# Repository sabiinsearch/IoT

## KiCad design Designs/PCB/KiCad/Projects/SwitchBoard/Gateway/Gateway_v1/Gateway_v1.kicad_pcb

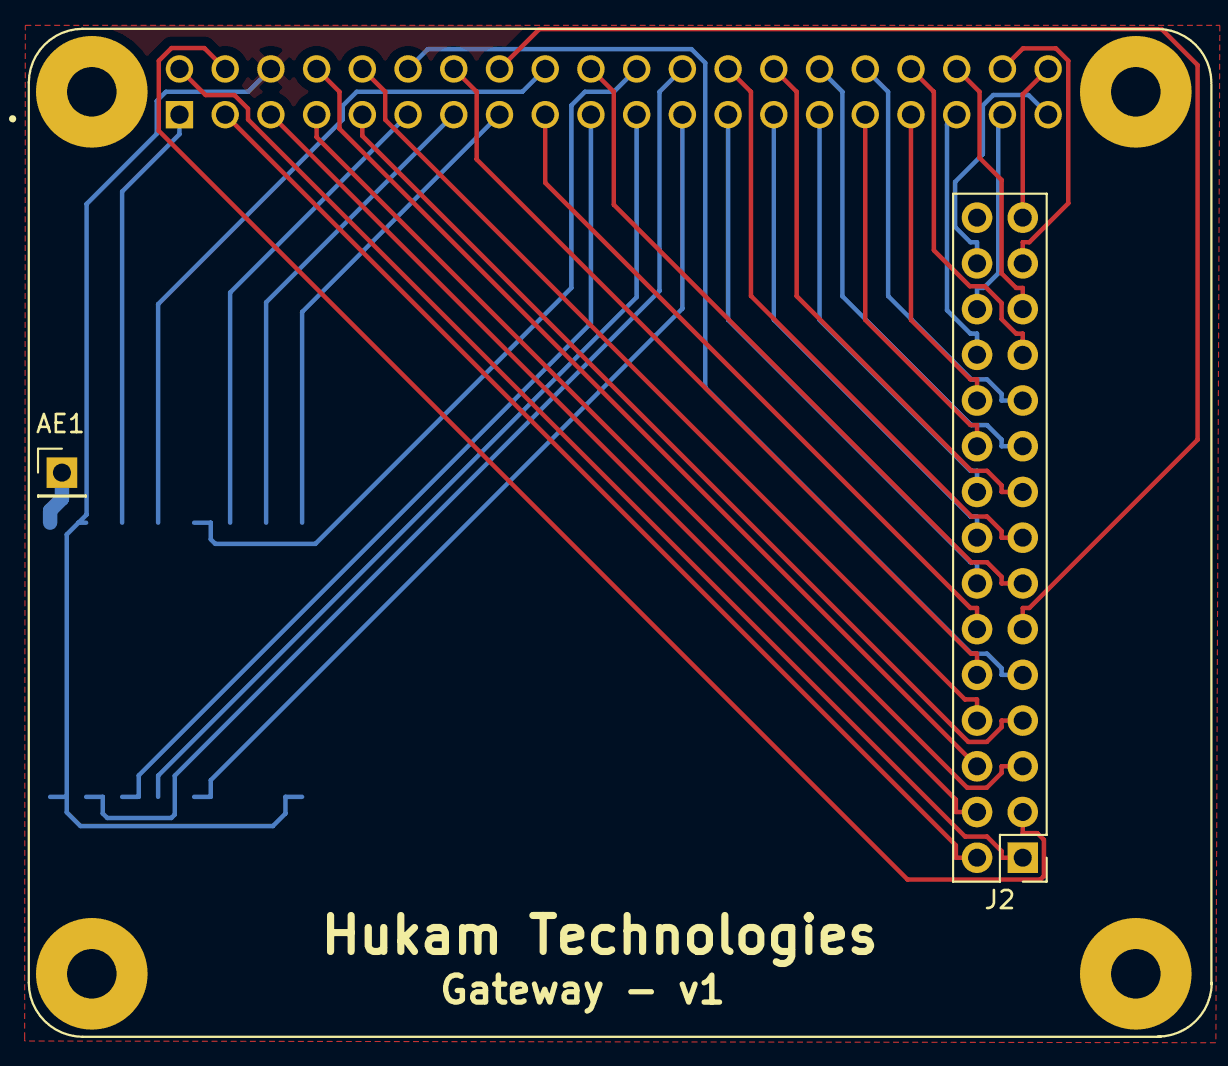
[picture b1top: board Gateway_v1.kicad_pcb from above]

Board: 2 copper layers, 4 parts (1 on the bottom side), 41 nets.

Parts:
AE1: Antenna; PinHeader_1x01_P2.54mm_Vertical
J1: Raspberry_Pi_2_3; MODULE_RASPBERRY_PI_3_MODEL_B+
J2: Conn_usable_pins; PinHeader_2x15_P2.54mm_Vertical
U1: LoRa

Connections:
/3.3v: J1.1, U1.3
/DIO0: J1.22, U1.5
/DIO1: J1.11, U1.6
/DIO2: J1.13, U1.7
/DIO3: J1.15, U1.8
/Gnd: J1.6, U1.2, U1.9, U1.16
/MISO: J1.21, U1.13
/MOSI: J1.19, U1.14
/NSS: J1.24, U1.15
/Pin_2: J1.2, J2.1
/Pin_3: J1.3, J2.2
/Pin_4: J1.4, J2.3
/Pin_5: J1.5, J2.4
/Pin_7: J1.7, J2.5
/Pin_8: J1.8, J2.6
/Pin_9: J1.9, J2.7
/Pin_10: J1.10, J2.8
/Pin_12: J1.12, J2.9
/Pin_14: J1.14, J2.10
/Pin_16: J1.16, J2.11
/Pin_17: J1.17, J2.12
/Pin_20: J1.20, J2.13
/Pin_25: J1.25, J2.14
/Pin_26: J1.26, J2.15
/Pin_27: J1.27, J2.16
/Pin_28: J1.28, J2.17
/Pin_29: J1.29, J2.18
/Pin_30: J1.30, J2.19
/Pin_31: J1.31, J2.20
/Pin_32: J1.32, J2.21
/Pin_33: J1.33, J2.22
/Pin_34: J1.34, J2.23
/Pin_35: J1.35, J2.24
/Pin_36: J1.36, J2.25
/Pin_37: J1.37, J2.26
/Pin_38: J1.38, J2.27
/Pin_39: J1.39, J2.28
/Pin_40: J1.40, J2.29
/Reset: J1.18, U1.4
/SCK: J1.23, U1.12
unnamed: AE1.1, U1.1

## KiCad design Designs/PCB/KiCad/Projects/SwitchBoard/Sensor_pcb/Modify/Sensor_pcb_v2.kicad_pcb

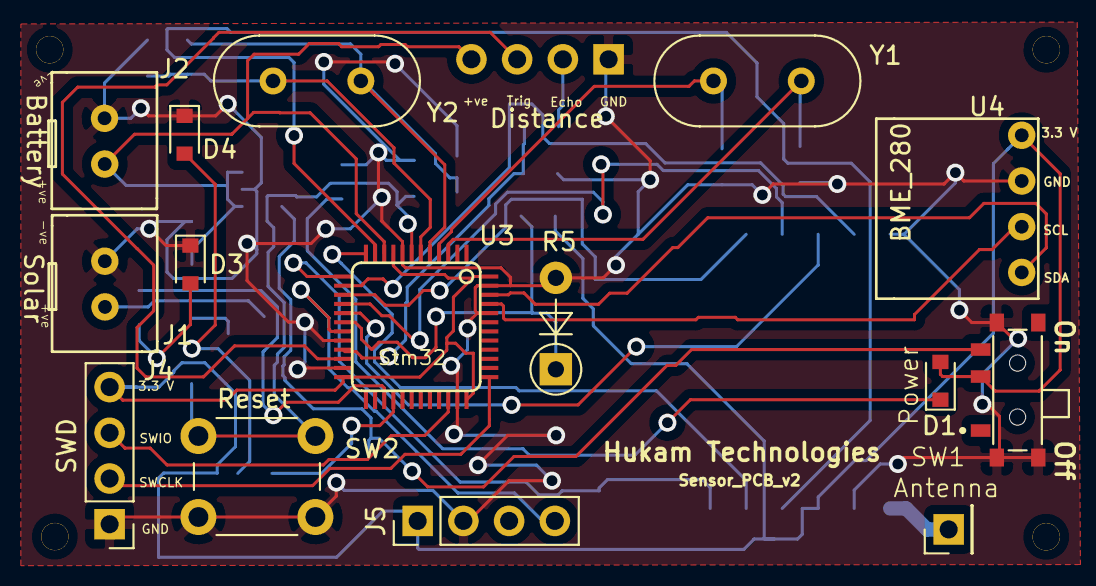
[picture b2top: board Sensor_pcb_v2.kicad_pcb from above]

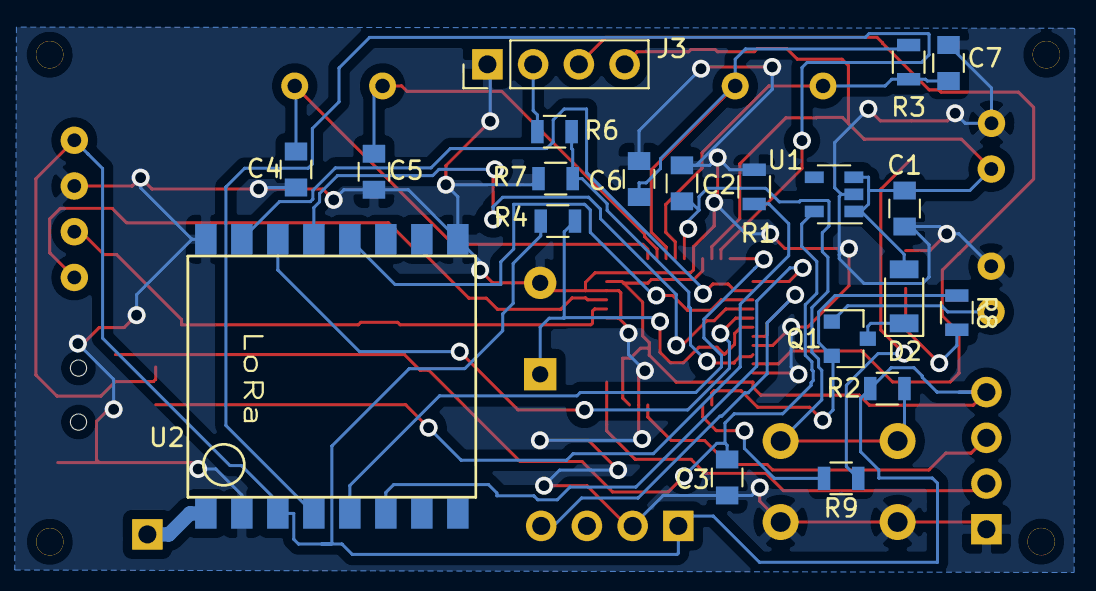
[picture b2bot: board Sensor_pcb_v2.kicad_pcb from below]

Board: 2 copper layers, 39 parts (20 on the bottom side), 33 nets.

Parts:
AE1: Antenna; Pin_Header_Straight_1x01_Pitch2.54mm
C1, C3: 100 nf; C_0805
C2: 1.0uf; C_0805
C4, C5, C6, C7: 20pf; C_0805
D1, D3: Pwr_L.E.D; D_0805
D2: DIODE; D_1206
D4: Bat_Low; D_0805
J1: Solar_input; Battery_holder
J2: Battery_input; Battery_holder
J3: Distance /; Pin_Header_Straight_1x04_Pitch2.54mm
J4: SWD; Pin_Header_Straight_1x04_Pitch2.54mm
J5: Airquality; Pin_Header_Straight_1x04_Pitch2.54mm
M1, M2, M3, M4: MountingHole_1.5mm; MountingHole1.5mm
Q1: BC547; SOT-23
R1, R8, R9: 510 R; R_0805
R2, R4: 10K; R_0805
R3: 1M; R_0805
R5: LDR; D_A-405_P5.08mm_Vertical_AnodeUp
R6: 2.7K; R_0805
R7: 4.7K; R_0805
SW1: MLL1200S; SW_MLL1200S
SW2: SW_Push; SW_PUSH_6mm_h5mm
U1: APK2112.K-3.3; SOT-23-5
U2: LoRa
U3: STM32; STM32(LQFP48)
U4: BME_280; BME280
Y1: 32.768K; Crystal_HC49-4H_Vertical
Y2: 8Mhz; Crystal_HC49-4H_Vertical

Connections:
/Air_in: J5.4, U3.19
/BAT_IN: C1.2, D2.2, J2.2, J3.4, U1.1, U1.3, U3.10
/Charge: Q1.2, R8.1, U3.27
/DIO0: U2.5, U3.12
/DIO1: U2.6, U3.13
/Echo: J3.2, R6.2
/EchoToStm32: R6.1, R7.2, U3.21
/GND: C1.1, C2.1, C3.1, C4.2, C5.2, C6.2, C7.2, D3.1, D4.1, J1.1, J2.1, J3.1, J4.1, J5.2, R1.2, R5.2, R7.1, SW1.G1, SW1.G2, SW1.G3, SW2.1, U1.2, U2.2, U2.9, U2.16, U3.8, U3.20, U3.23, U3.35, U3.44, U3.47, U4.2
/LDR_IN: R4.1, R5.1, U3.18
/MISO: U2.13, U3.16
/MOSI: U2.14, U3.17
/NSS: U2.15, U3.14
/OSCIN: C6.1, R3.1, U3.5, Y2.1
/OSCOUT: C7.1, R3.2, U3.6, Y2.2
/PC14: C4.1, U3.3, Y1.1
/PC15: C5.1, U3.4, Y1.2
/RESET: C2.2, R2.2, SW2.2, U3.7
/Reset_LoRa: U2.4, U3.11
/SCK: U2.12, U3.15
/SCL: U3.45, U4.3
/SDA: U3.46, U4.4
/SWCLK: J4.2, U3.37
/SWIO: J4.3, U3.34
/Solar_+ve: J1.2, Q1.1
/Supply_Reg: C3.2, SW1.3, U1.5
/Trig: J3.3, U3.22
/VCC3V3: D1.2, J4.4, J5.1, R2.1, R4.2, SW1.2, U2.3, U3.9, U3.24, U3.36, U3.48, U4.1
unnamed: AE1.1, U2.1
unnamed: D1.1, R1.1
unnamed: D2.1, Q1.3
unnamed: D3.2, R8.2
unnamed: D4.2, R9.1
unnamed: R9.2, U3.28

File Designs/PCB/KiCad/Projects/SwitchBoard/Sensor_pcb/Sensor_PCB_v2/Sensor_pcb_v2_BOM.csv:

Reference,,Quantity,,Footprint / package,,,,Datasheet,,Spice_Netlist_Enabled,,Spice_Primitive
AE1,,1,Antenna,Pin_Headers:Pin_Header_Straight_1x01_Pitch2.54mm,,,,,,,,
C2,,1,1.0uf,Capacitors_SMD:C_0805,,,,,,,,
"C1, C3",,2,100nf,Capacitors_SMD:C_0805,,,,,,,,
"C4, C5, C6, C7",,4,20pf,Capacitors_SMD:C_0805,,,,~,,,,
"D1, D3",,2,Pwr_L.E.D,Diodes_SMD:D_0805,,,,,,,,
D2,,1,DIODE,Diodes_SMD:D_1206,,,,,,,,
D4,,1,Bat_Low,Diodes_SMD:D_0805,,,,,,,,
J1,,1,Solar_input,Custom_Libraries:Battery_holder,,,,,,,,
J2,,1,Battery_input,Custom_Libraries:Battery_holder,,,,,,,,
J3,,1,Distance /,Pin_Headers:Pin_Header_Straight_1x04_Pitch2.54mm,,,,,,,,
J4,,1,SWD,Pin_Headers:Pin_Header_Straight_1x04_Pitch2.54mm,,,,,,,,
J5,,1,Airquality,Pin_Headers:Pin_Header_Straight_1x04_Pitch2.54mm,,,,,,,,
Q1,,1,BC547,TO_SOT_Packages_SMD:SOT-23,,,,,,,,
"R1, R8, R9",,3,510 R,Resistors_SMD:R_0805,,,,,,,,
"R2, R4",,2,10K,Resistors_SMD:R_0805,,,,,,,,
R3,,1,1M,Resistors_SMD:R_0805,,,,,,,,
R5,,1,LDR,Diodes_THT:D_A-405_P5.08mm_Vertical_AnodeUp,,,,,,,,
R6,,1,2.7K,Resistors_SMD:R_0805,,,,,,,,
R7,,1,4.7K,Resistors_SMD:R_0805,,,,,,,,
SW1,,1,MLL1200S,Custom_Libraries:SW_MLL1200S,,,,,,,,
SW2,,1,SW_Push,Buttons_Switches_THT:SW_PUSH_6mm_h5mm,,,,,,,,
U1,,1,APK2112.K-3.3,TO_SOT_Packages_SMD:SOT-23-5,,,,,,,,
U2,,1,LoRa,Custom_Libraries:LoRa,,,,,,,,
U3,,1,STM32,Custom_Libraries:STM32(LQFP48),,,,,,,,
U4,,1,BME_280,Custom_Libraries:BME280,,,,,,,,
Y1,,1,32.768K,Crystals:Crystal_HC49-4H_Vertical,,,,,,,,
Y2,,1,8Mhz,Crystals:Crystal_HC49-4H_Vertical,~,,,,,,,

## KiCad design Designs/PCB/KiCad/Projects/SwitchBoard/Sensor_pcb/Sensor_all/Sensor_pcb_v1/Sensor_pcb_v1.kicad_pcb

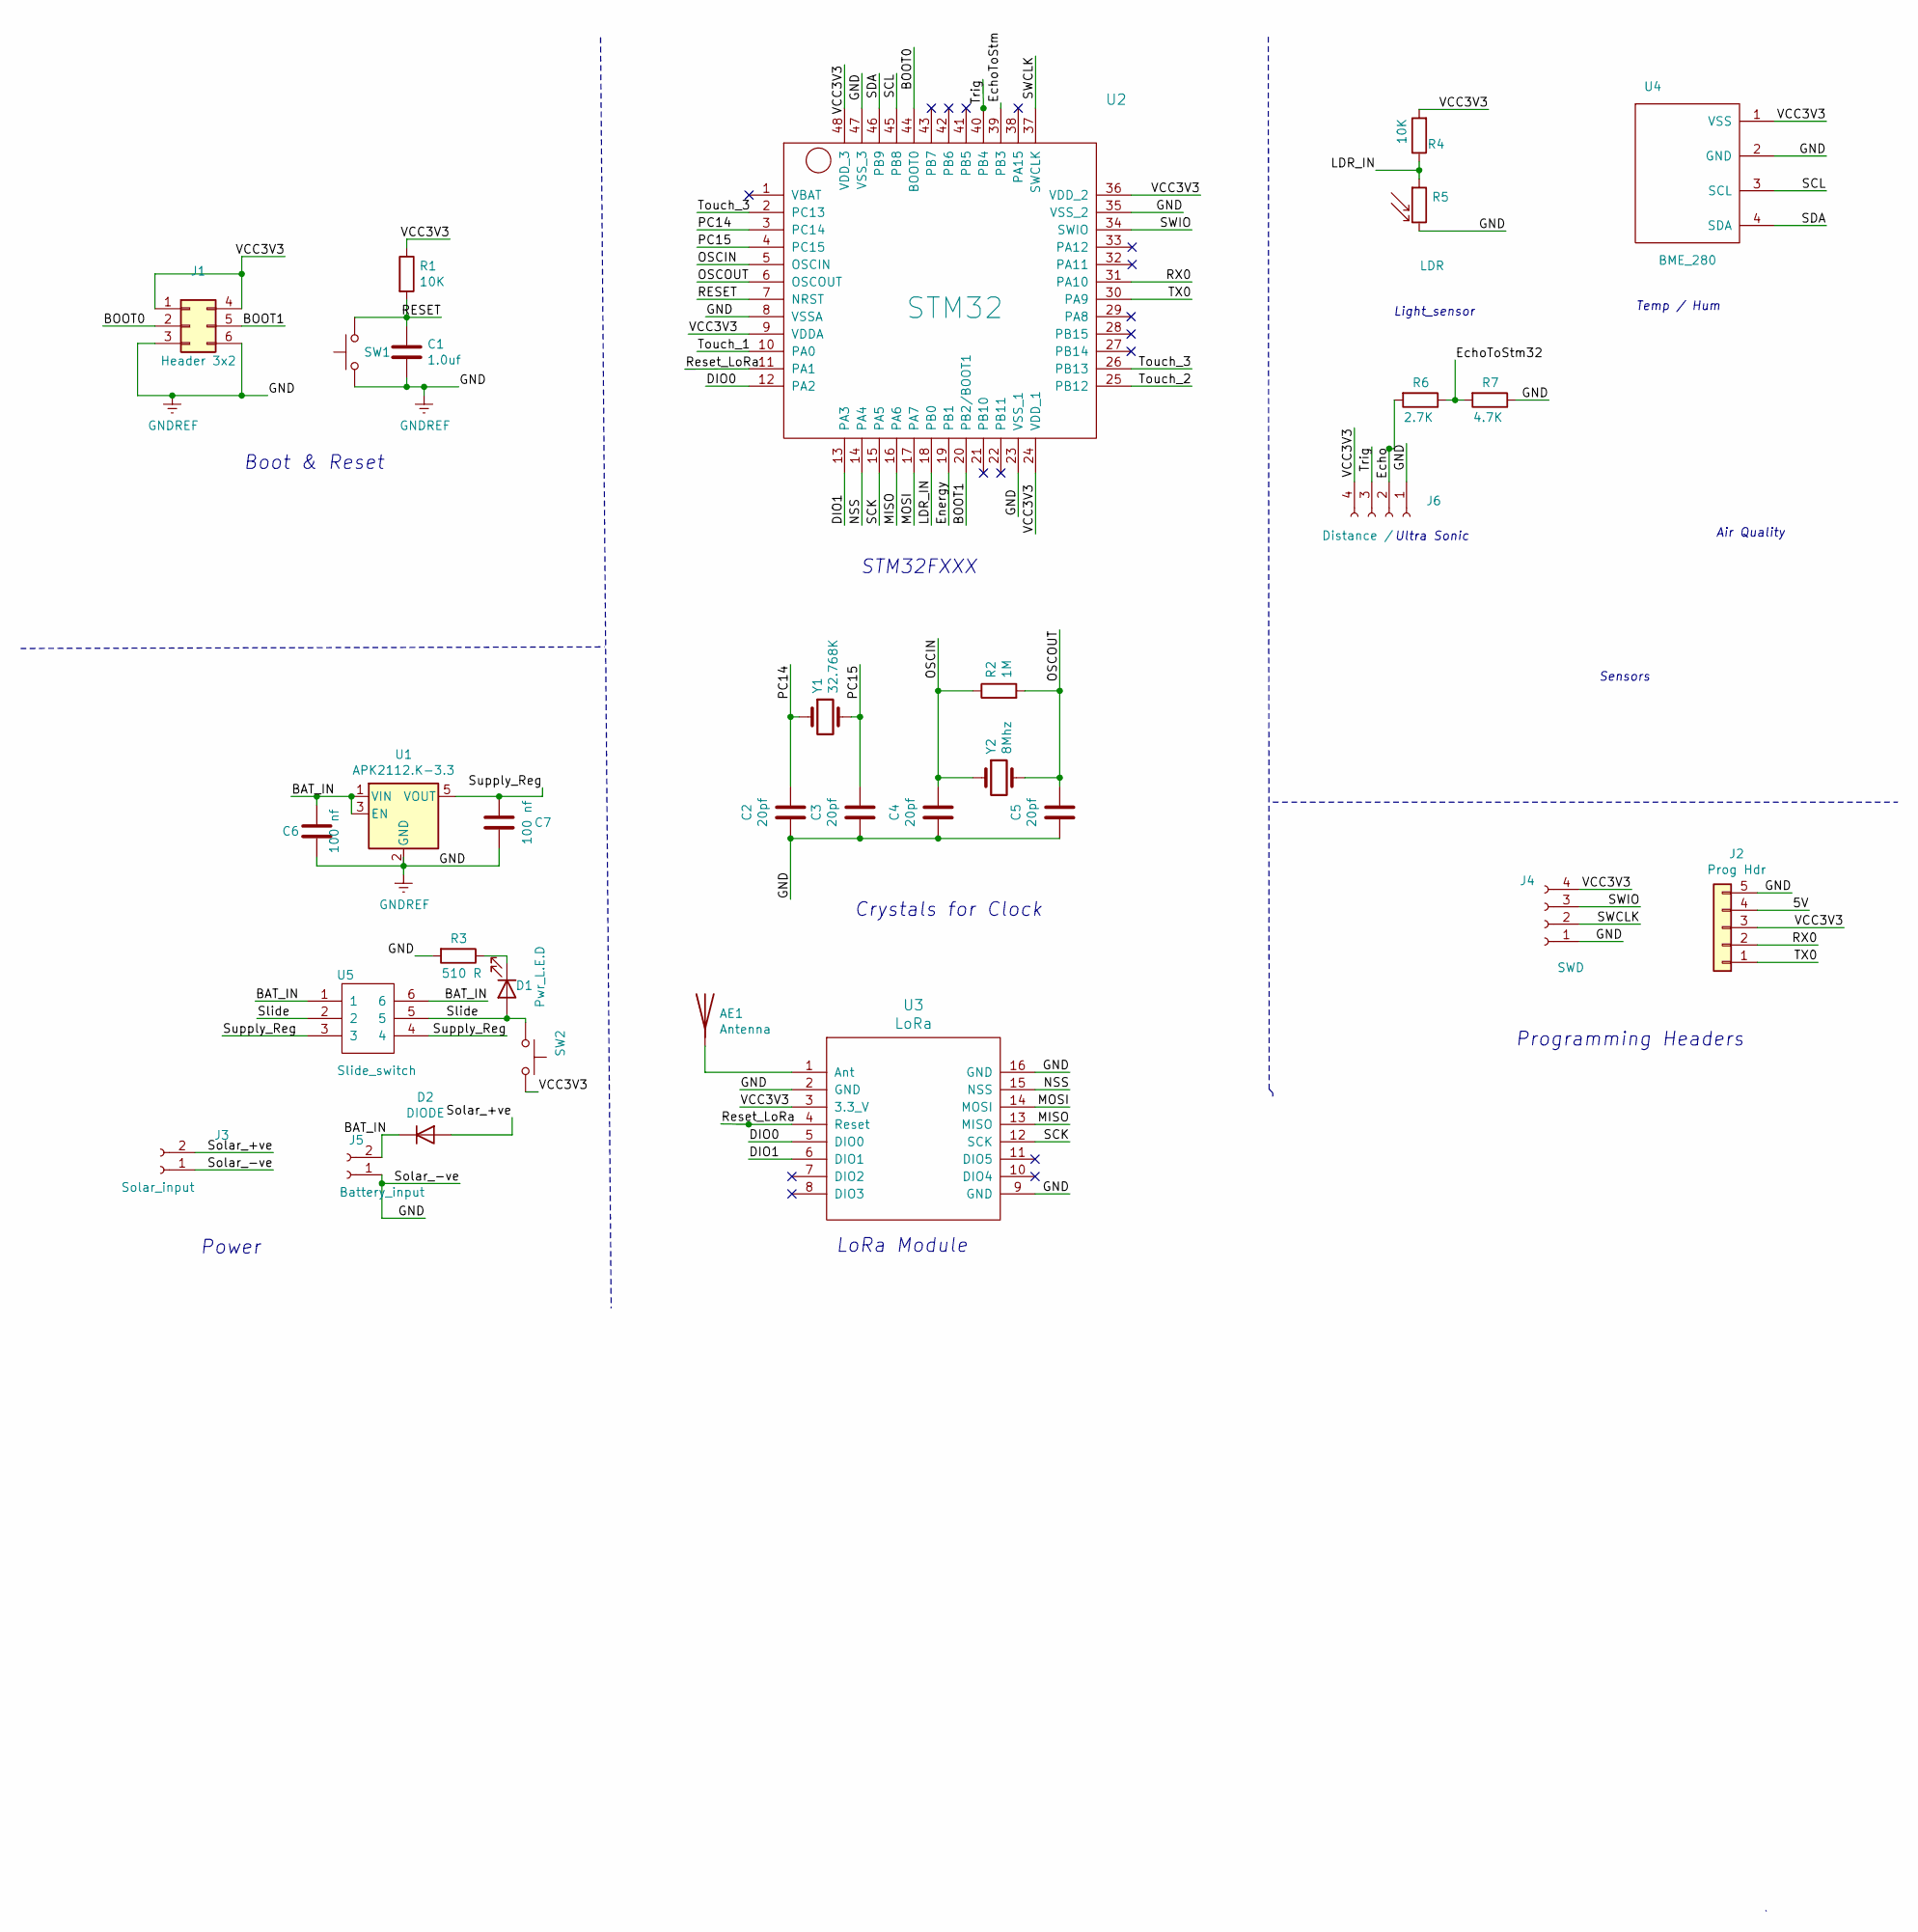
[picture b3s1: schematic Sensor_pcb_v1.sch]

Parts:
AE1: Antenna; Pin_Header_Straight_1x01_Pitch2.54mm
C1: 1.0uf; C_0805
C2, C3, C4, C5: 20pf; C_0805
C6, C7: 100 nf; C_0805
D1: Pwr_L.E.D; D_0805
D2: DIODE; D_0805
J1: Header 3x2; Pin_Header_02x03
J2: Prog Hdr; Pin_Header_Straight_1x05_Pitch2.54mm
J3: Solar_input; Battery_holder
J4: SWD; Pin_Header_Straight_1x04_Pitch2.54mm
J5: Battery_input; Battery_holder
J6: Distance /; Pin_Header_Straight_1x04_Pitch2.54mm
R1, R4: 10K; R_0805
R2: 1M; R_0805
R3: 510 R; R_0805
R5: LDR; D_A-405_P5.08mm_Vertical_AnodeUp
R6: 2.7K; R_0805
R7: 4.7K; R_0805
SW1: SW_Push; SW_DIP_x1_W7.62mm_Slide_Copal_CHS-B
SW2: SW_Push; SW_PUSH_6mm_h5mm
U1: APK2112.K-3.3; SOT-23-5
U2: STM32; STM32(LQFP48)
U3: LoRa
U4: BME_280; BME280
U5: Slide_switch; SW_DIP_x3_W7.62mm_Slide_LowProfile
Y1: 32.768K; Crystal_HC49-4H_Vertical
Y2: 8Mhz; Crystal_HC49-4H_Vertical

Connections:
/5V: J2.4
/BAT_IN: C6.2, D2.2 (K), J5.2, U1.1 (VIN), U1.3 (EN), U5.1, U5.6
/BOOT0: J1.2, U2.44 (BOOT0)
/BOOT1: J1.5, U2.20 (PB2/BOOT1)
/DIO0: U2.12 (PA2), U3.5 (DIO0)
/DIO1: U2.13 (PA3), U3.6 (DIO1)
/Echo: J6.2, R6.2
/EchoToStm: U2.39 (PB3)
/EchoToStm32: R6.1, R7.2
/Energy: U2.19 (PB1)
/LDR_IN: R4.1, R5.1, U2.18 (PB0)
/MISO: U2.16 (PA6), U3.13 (MISO)
/MOSI: U2.17 (PA7), U3.14 (MOSI)
/NSS: U2.14 (PA4), U3.15 (NSS)
/OSCIN: C4.1, R2.1, U2.5 (OSCIN), Y2.1
/OSCOUT: C5.1, R2.2, U2.6 (OSCOUT), Y2.2
/PC14: C2.1, U2.3 (PC14), Y1.1
/PC15: C3.1, U2.4 (PC15), Y1.2
/RESET: C1.2, R1.2, SW1.2, U2.7 (NRST)
/RX0: J2.2, U2.31 (PA10)
/Reset_LoRa: U2.11 (PA1), U3.4 (Reset)
/SCK: U2.15 (PA5), U3.12 (SCK)
/SCL: U2.45 (PB8), U4.3 (SCL)
/SDA: U2.46 (PB9), U4.4 (SDA)
/SWCLK: J4.2, U2.37 (SWCLK)
/SWIO: J4.3, U2.34 (SWIO)
/Slide: D1.2 (A), SW2.1, U5.2, U5.5
/Solar_+ve: D2.1 (A), J3.2
/Supply_Reg: C7.2, U1.5 (VOUT), U5.3, U5.4
/TX0: J2.1, U2.30 (PA9)
/Trig: J6.3, U2.40 (PB4)
/VCC3V3: J1.1, J1.4, J2.3, J4.4, J6.4, R1.1, R4.2, SW2.2, U2.9 (VDDA), U2.24 (VDD_1), U2.36 (VDD_2), U2.48 (VDD_3), U3.3 (3.3_V), U4.1 (VSS)
GNDREF: C1.1, C2.2, C3.2, C4.2, C5.2, C6.1, C7.1, J1.3, J1.6, J2.5, J3.1, J4.1, J5.1, J6.1, R3.2, R5.2, R7.1, SW1.1, U1.2 (GND), U2.8 (VSSA), U2.23 (VSS_1), U2.35 (VSS_2), U2.47 (VSS_3), U3.2 (GND), U3.9 (GND), U3.16 (GND), U4.2 (GND)
unnamed: AE1.1, U3.1 (Ant)
unnamed: D1.1 (K), R3.1

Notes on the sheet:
Programming Headers
Power
Boot & Reset
LoRa Module
Sensors
Temp / Hum
Light_sensor
Air Quality
STM32FXXX
Crystals for Clock
Ultra Sonic

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
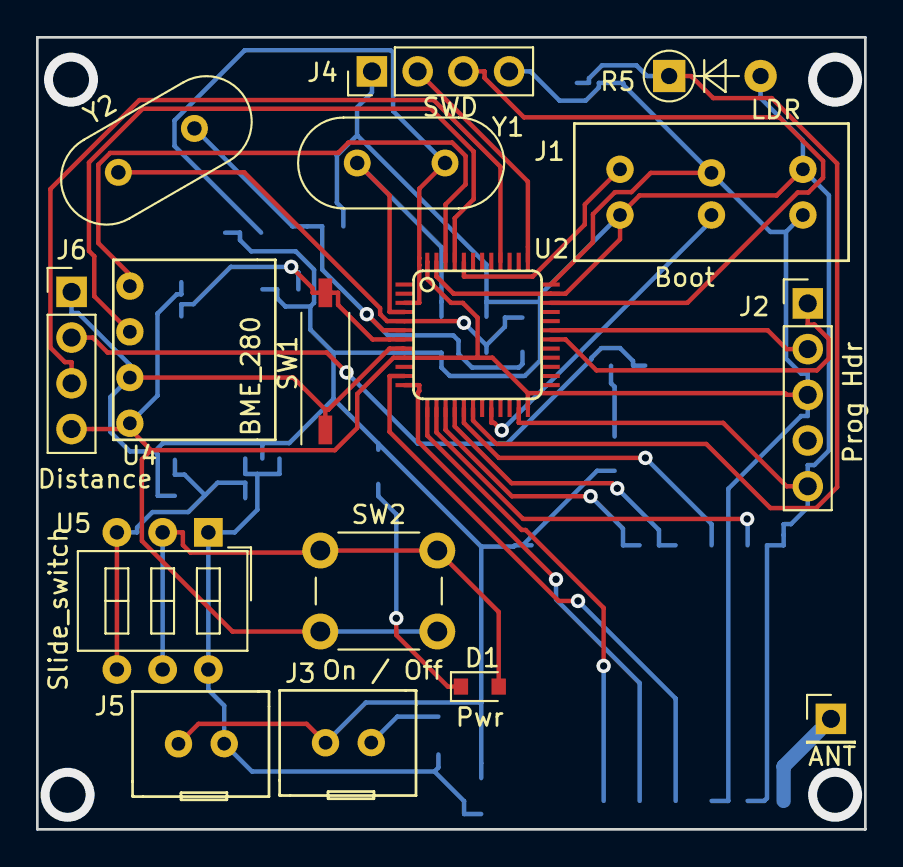
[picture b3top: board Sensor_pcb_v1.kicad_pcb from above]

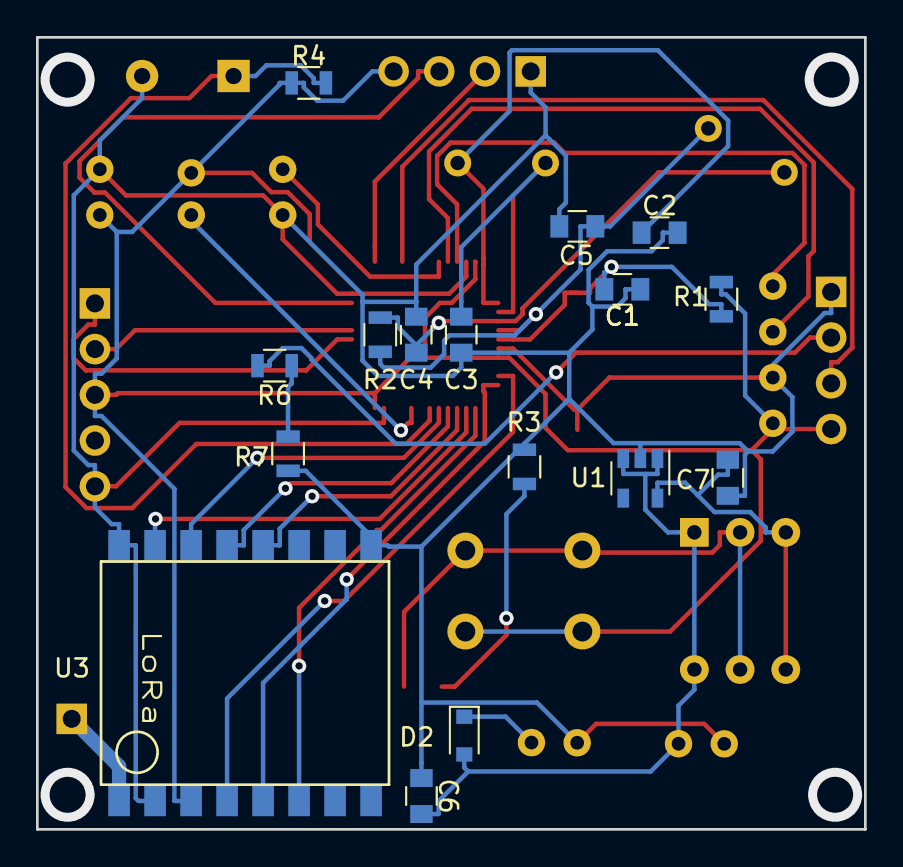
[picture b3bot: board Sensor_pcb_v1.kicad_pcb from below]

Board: 2 copper layers, 46.0 x 44.0 mm, 32 parts (16 on the bottom side), 32 nets.

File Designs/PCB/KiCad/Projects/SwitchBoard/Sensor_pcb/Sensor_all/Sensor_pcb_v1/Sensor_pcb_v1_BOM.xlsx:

Id | Designator | Package | Quantity | Designation | Supplier | and | ref | Source | Cost per head | Total Cost
1 | U2 | STM32(LQFP48) | 1 | STM32F108C8T6 |  |  |  | Robu.com | 199 | 199
2 | SW1 | SW_SPST_B3U-1000P | 1 | Tacticle_Switch |  |  |  |  | 0 | 0
3 | U3 | LoRa | 1 | LoRa |  |  |  | Robu.com | 449 | 449
4 | AE1 | Pin_Header_Straight_1x01_Pitch2.54mm | 1 | Antenna |  |  |  |  | 0 | 0
5 | R7 | R_0805 | 1 | 4.7K |  |  |  | Amazon.com | 1 | 1
6 | R6 | R_0805 | 1 | 2.7K |  |  |  | Amazon.com | 1 | 1
7 | J6 | Pin_Header_Straight_1x04_Pitch2.54mm | 1 | Male | Headers_01x04_Pitch_2.54mm |  |  | Amazon.com | 2 | 2
8 | J5,J3 | JST XH 2.54mm pitch | 2 | Lipo_Battery_Connector |  |  |  | Amazon.com | 7 | 14
9 | SW2 | SW_PUSH_6mm_h5mm | 1 | Slide_Switch |  |  |  | Amazon.com | 8 | 79
10 | U5 | SW_DIP_x3_W7.62mm_Slide_LowProfile | 1 | Slide_switch |  |  |  | Amazon.com | 8 | 8
11 | C1 | C_0805 | 1 | 1.0uf |  |  |  | Amazon.com | 1 | 1
12 | C2,C3,C4,C5 | C_0805 | 4 | 20pf |  |  |  | Amazon.com | 2 | 8
13 | C6,C7 | C_0805 | 2 | 100 | nf |  |  | Amazon.com | 1 | 2
14 | D1 | D_0805 | 1 | Pwr_L.E.D |  |  |  | Amazon.com | 1 | 1
15 | D2 | D_0805 | 1 | IN4007 |  |  |  | Amazon.com | 1 | 1
16 | J1 | Pin_Header_02x03 | 1 | Boot |  |  |  | Amazon.com | 3 | 3
17 | J2 | Pin_Header_Straight_1x05_Pitch2.54mm | 1 | Headers_1x05_Pitch_2.54mm |  |  |  | Amazon.com | 2.5 | 2.5
18 | J4 | Pin_Header_Straight_1x04_Pitch2.54mm | 1 | SWD |  |  |  | Amazon.com | 2 | 2
19 | R1,R4 | R_0805 | 2 | 10K |  |  |  | Amazon.com | 1 | 2
20 | R2 | R_0805 | 1 | 1M |  |  |  | Amazon.com | 1 | 1
21 | R3 | R_0805 | 1 | 510 | R |  |  | Amazon.com | 1 | 1
22 | R5 | D_A-405_P5.08mm_Vertical_AnodeUp | 1 | LDR |  |  |  | Amazon.com | 6 | 6
23 | U1 | SOT-23-5 | 1 | APK2112.K-3.3 |  |  |  | Amazon.com | 5 | 5
24 | U4 | BME280 | 1 | BME_280 |  |  |  | Amazon.com | 495 | 495
25 | Y1 | Crystal_HC49-4H_Vertical | 1 | 32.768K |  |  |  | Robu.com | 59 | 59
26 | Y2 | Crystal_HC49-4H_Vertical | 1 | 8Mhz |  |  |  | Robu.com | 59 | 59
 |  |  |  |  |  |  |  |  | Total Cost | 1401.5
